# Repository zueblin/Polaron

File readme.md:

# Polaron

Polaron is a DIY digital drum machine based on the [Teensy 3.6](https://www.pjrc.com/teensy/) USB Microcontroller plattform.

Main features:

- 16 step sequencer
- 6 instrument tracks
- 16 patterns per track
- load/save projects to SD card
- 2 pots for parameter control
- parameter locks: all instrument parameters can be recorded for each step
- different pattern length for each instrument track
- sync to midi-clock (usb-midi) or trigger input
- crunchy 12bit stereo outputs
- open source hardware/software: if you miss a feature or are annoyed by a bug... change it!

Disclaimer: This is a DIY project, features may change or not work for you. Use at your own risk.

here's some short videos:

https://www.youtube.com/watch?v=JC_pZTxMb0c

https://vimeo.com/302283771

https://vimeo.com/305113707

Follow the project on Instagram: https://www.instagram.com/polaron.me/

And don't forget to check the [Project WIKI](https://github.com/zueblin/Polaron/wiki) for more info.

## Software

To build the software, the following tools are required:

- [Arduino IDE](https://www.arduino.cc/en/Main/Software) (tested with 1.8.6)
- [Teensyduino Add-On](https://www.pjrc.com/teensy/teensyduino.html) (tested with 1.43)

## Hardware

PCB is designed using KICAD 5.1.2

Parts needed (Rev 1.4):

- Teensy 3.6 32bit Microcontroller (with Headers)
- 30 x WS2812b RGB LEDs (or SK6812)
- 30 x 6x6mm Pushbuttons (ideally 4.3mm height, 100gf) (Mouser: 688-SKHHAJ)
- 16 x 270 ohm throughhole Resistors (Mouser: 603-MF0207FTE52-270R)
- 14 x 270 ohm SMD Resistors (1206 housing)
- 2 x 10k SMD Resistors (1206 housing)
- 1 x 1N4148 diode
- 1 x 2N3904BU transistor
- 4 x SN74HC165N Shiftregister (Mouser: 595-SN74HC165N)
- 2 x ALPS Potentiometer (RK09K1130A8G)
- 2 x 2.2 uF SMD Capacitor (1206 housing, Mouser: 963-TMK316BJ225KL-T)
- 2 x Audio Jack (SJ-352X-SMT)
- 1 x 48 Position / 2 Row IC DIP Socket (Mouser: 517-4848-6004-CP)
- 2 x 20mm PCB Standoff with 3mm thread (Mouser: 534-24437)

Check the Wiki for [Build Instructions](https://github.com/zueblin/Polaron/wiki/Building-the-Polaron)

## Known Issues:
PCB Rev 1.4

- In some situations, when connecting the polaron to a computer via usb and connecting the polaron audio output to an audio interface that is connected to the computer (e.g via thunderbolt), a ground loop is created. This results in a very noticable noise/whine in the audio channel (which is caused by the LED PWM). Tested solution: [Audio Ground Loop Noise Isolator](https://www.pjrc.com/store/audio_ground_isolator.html)

## FAQ

- Q: Is this an easy build? A: This is an intermediate project to build. Its not very complicated, but there are some SMD parts which are not easy to get right (the LEDs). You'll need a decent soldering iron, with a rather fine tip.
- Q: Is this a pro audio project? A: No, not exactly. The Polaron is more about a fun workflow than super hifi sound.
- Q: Does it work with a Teensy 3.5? A: PJRC forum member drjohn reports successfully running the Polaron with a Teensy 3.5.
- Q: Does it work with a Teensy 4.0 / 4.1? A: No, the Polaron relies on the internal DAC of the Teensy 3.6 and is not compatible with Teensy 4.0 / 4.1
- Q: Is there a manual? A: Yes, please check the [Project WIKI](https://github.com/zueblin/Polaron/wiki) for build instructions and operating manual. If you still have questions / suggestions, please send me a mail.
- Q: Does the polaron fit into a euro-rack? A: No, not really (PCB size is 15.7cm x 11.6cm). Polaron builder N.Shaver has experimented with a 3D printable eurorack case for the polaron which he shares on [Thingiverse](https://www.thingiverse.com/thing:3830556)
- Q: Can i buy a PCB? A: Sold out, but let me know if you'd be interested in buying one. ~~Yes, i currently have PCBs at 15 USD (+ shipping from switzerland). Please contact me by email, if interested.~~
- Q: Can i buy a part-kit? A: I don't sell part kits anymore, since it is very easy and efficient to order parts online, eg. from mouser. ~~Yes, i currently have part kits (PCB + all parts, EXCLUDING the teensy itself) at 60 USD incl. untracked international shipping. Add 5 USD for tracked shipping. Please send me a mail, if interested.~~
- Q: Can i buy a fully assembled Polaron? A: Not, not at the moment.
- Q: How can i support this project? A: Spread the word, star the project on github, let your friends know, buy a PCB, build a Polaron and share a video...there are many ways. In general, knowing that this project sparks some interest is what keeps it going!

# License

Code: MIT

Hardware: cc-by-sa-3.0

By: Thomas Zueblin (thomas.zueblin@gmail.com)

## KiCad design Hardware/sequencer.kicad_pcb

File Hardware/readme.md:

# License

Code: MIT

Hardware: cc-by-sa-3.0

By: Thomas Zueblin (thomas.zueblin@gmail.com)

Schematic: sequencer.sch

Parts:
C1, C2: 2.2uF; C_1206_HandSoldering
D1, D2, D3, D4, D5, D6, D7, D8, D9, D10, D11, D12, D13, D14, D15, D16, D17, D18, D19, D20, D21, D22, D23, D24, D25, D26, D27, D28, D29, D30: LED_WS2812B-PLCC4
D31: 1N4148; D_DO-35_SOD27_P2.54mm_Vertical_AnodeUp
IC1, IC2, IC3, IC4: 74HC165N; DIL16
J1, J2: SJ-3523-SMT-TR; CUI_SJ-3523-SMT-TR
Q1: 2N3904; TO-92_Inline_Wide
R1, R2, R3, R4, R5, R6, R7, R8, R9, R10, R11, R12, R13, R14, R15, R16: 270; R_Axial_DIN0411_L9.9mm_D3.6mm_P12.70mm_Horizontal_noSilkscr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
R17, R18, R19, R20, R21, R22, R23, R24, R25, R26, R27, R28, R29, R30: 270; R_1206_HandSoldering
R31, R32: 10k; R_1206_HandSoldering
RV1, RV2: POT; Potentiometer_Alps_RK09K_Horizontal
S1, S2, S3, S4, S5, S6, S7, S8, S9, S10, S11, S12, S13, S14, S15, S16, S17, S18, S19, S20, S21, S22, S23, S24, S25, S26, S27, S28, S29, S30: SWITCH-MOMENTARY-2PTH; TACTILE-PTH
U1: Teensy3.6; Teensy35_36_simple

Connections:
/Audio1: C1.2, J1.3
/Audio2: C2.2, J1.2
/AudioGND: J1.1, U1.52 (AGND)
/JOY_A: RV1.2, U1.50 (23_A9_PWM_Touch)
/JOY_B: RV2.2, U1.49 (22_A8_PWM_Touch)
/LED_IN: D1.4 (DIN), U1.8 (6_PWM)
/LedConn1: D8.2 (DOUT), D9.4 (DIN)
/LedConn2: D16.2 (DOUT), D17.4 (DIN)
/LedConn3: D24.2 (DOUT), D25.4 (DIN)
/SHIFT_CLOCK: IC1.2 (CLK), IC2.2 (CLK), IC3.2 (CLK), IC4.2 (CLK), U1.4 (2_PWM)
/SHIFT_DATA_OUT: IC4.9 (QH), U1.3 (1_TX1_MISO1_Touch)
/SHIFT_PLOAD: IC1.1 (SH/~LD), IC2.1 (SH/~LD), IC3.1 (SH/~LD), IC4.1 (SH/~LD), U1.2 (0_RX1_MOSI1_Touch)
/Trigger-Input: Q1.3, R32.1, U1.30 (33_A14_CAN1TX_scl0)
GND: D1.3 (VSS), D2.3 (VSS), D3.3 (VSS), D4.3 (VSS), D5.3 (VSS), D6.3 (VSS), D7.3 (VSS), D8.3 (VSS), D9.3 (VSS), D10.3 (VSS), D11.3 (VSS), D12.3 (VSS), D13.3 (VSS), D14.3 (VSS), D15.3 (VSS), D16.3 (VSS), D17.3 (VSS), D18.3 (VSS), D19.3 (VSS), D20.3 (VSS), D21.3 (VSS), D22.3 (VSS), D23.3 (VSS), D24.3 (VSS), D25.3 (VSS), D26.3 (VSS), D27.3 (VSS), D28.3 (VSS), D29.3 (VSS), D30.3 (VSS), D31.2, IC1.8 (GND), IC1.15 (INH), IC2.8 (GND), IC2.15 (INH), IC3.8 (GND), IC3.15 (INH), IC4.5 (G), IC4.6 (H), IC4.8 (GND), IC4.15 (INH), J2.1, Q1.1, R1.2, R2.2, R3.2, R4.2, R5.2, R6.2, R7.2, R8.2, R9.2, R10.2, R11.2, R12.2, R13.2, R14.2, R15.2, R16.2, R17.1, R18.1, R19.1, R20.1, R21.1, R22.1, R23.1, R24.1, R25.1, R26.1, R27.1, R28.1, R29.1, R30.1, RV1.3, RV2.3, U1.1 (GND)
unnamed: C1.1, U1.37 (A21_DAC0)
unnamed: C2.1, U1.38 (A22_DAC1)
unnamed: D1.2 (DOUT), D2.4 (DIN)
unnamed: D2.2 (DOUT), D3.4 (DIN)
unnamed: D3.2 (DOUT), D4.4 (DIN)
unnamed: D4.2 (DOUT), D5.4 (DIN)
unnamed: D5.2 (DOUT), D6.4 (DIN)
unnamed: D6.2 (DOUT), D7.4 (DIN)
unnamed: D7.2 (DOUT), D8.4 (DIN)
unnamed: D10.2 (DOUT), D11.4 (DIN)
unnamed: D9.2 (DOUT), D10.4 (DIN)
unnamed: D11.2 (DOUT), D12.4 (DIN)
unnamed: D12.2 (DOUT), D13.4 (DIN)
unnamed: D13.2 (DOUT), D14.4 (DIN)
unnamed: D14.2 (DOUT), D15.4 (DIN)
unnamed: D15.2 (DOUT), D16.4 (DIN)
unnamed: D17.2 (DOUT), D18.4 (DIN)
unnamed: D18.2 (DOUT), D19.4 (DIN)
unnamed: D19.2 (DOUT), D20.4 (DIN)
unnamed: D20.2 (DOUT), D21.4 (DIN)
unnamed: D21.2 (DOUT), D22.4 (DIN)
unnamed: D22.2 (DOUT), D23.4 (DIN)
unnamed: D23.2 (DOUT), D24.4 (DIN)
unnamed: D25.2 (DOUT), D26.4 (DIN)
unnamed: D26.2 (DOUT), D27.4 (DIN)
unnamed: D27.2 (DOUT), D28.4 (DIN)
unnamed: D28.2 (DOUT), D29.4 (DIN)
unnamed: D29.2 (DOUT), D30.4 (DIN)
unnamed: D31.1, Q1.2, R31.2
unnamed: IC1.3 (E), R21.2, S21.3 (2)
unnamed: IC1.4 (F), R22.2, S22.3 (2)
unnamed: IC1.5 (G), R23.2, S23.3 (2)
unnamed: IC1.6 (H), R24.2, S24.3 (2)
unnamed: IC1.9 (QH), IC2.10 (SER)
unnamed: IC1.11 (A), R17.2, S17.3 (2)
unnamed: IC1.12 (B), R18.2, S18.3 (2)
unnamed: IC1.13 (C), R19.2, S19.3 (2)
unnamed: IC1.14 (D), R20.2, S20.3 (2)
unnamed: IC2.3 (E), R13.1, S13.3 (2)
unnamed: IC2.4 (F), R14.1, S14.3 (2)
unnamed: IC2.5 (G), R15.1, S15.3 (2)
unnamed: IC2.6 (H), R16.1, S16.3 (2)
unnamed: IC2.9 (QH), IC3.10 (SER)
unnamed: IC2.11 (A), R9.1, S9.3 (2)
unnamed: IC2.12 (B), R10.1, S10.3 (2)
unnamed: IC2.13 (C), R11.1, S11.3 (2)
unnamed: IC2.14 (D), R12.1, S12.3 (2)
unnamed: IC3.3 (E), R5.1, S5.3 (2)
unnamed: IC3.4 (F), R6.1, S6.3 (2)
unnamed: IC3.5 (G), R7.1, S7.3 (2)
unnamed: IC3.6 (H), R8.1, S8.3 (2)
unnamed: IC3.9 (QH), IC4.10 (SER)
unnamed: IC3.11 (A), R1.1, S1.3 (2)
unnamed: IC3.12 (B), R2.1, S2.3 (2)
unnamed: IC3.13 (C), R3.1, S3.3 (2)
unnamed: IC3.14 (D), R4.1, S4.3 (2)
unnamed: IC4.3 (E), R29.2, S29.3 (2)
unnamed: IC4.4 (F), R30.2, S30.3 (2)
unnamed: IC4.11 (A), R25.2, S25.3 (2)
unnamed: IC4.12 (B), R26.2, S26.3 (2)
unnamed: IC4.13 (C), R27.2, S27.3 (2)
unnamed: IC4.14 (D), R28.2, S28.3 (2)
unnamed: J2.2, R31.1
VCC: D1.1 (VDD), D2.1 (VDD), D3.1 (VDD), D4.1 (VDD), D5.1 (VDD), D6.1 (VDD), D7.1 (VDD), D8.1 (VDD), D9.1 (VDD), D10.1 (VDD), D11.1 (VDD), D12.1 (VDD), D13.1 (VDD), D14.1 (VDD), D15.1 (VDD), D16.1 (VDD), D17.1 (VDD), D18.1 (VDD), D19.1 (VDD), D20.1 (VDD), D21.1 (VDD), D22.1 (VDD), D23.1 (VDD), D24.1 (VDD), D25.1 (VDD), D26.1 (VDD), D27.1 (VDD), D28.1 (VDD), D29.1 (VDD), D30.1 (VDD), IC1.16 (VCC), IC2.16 (VCC), IC3.16 (VCC), IC4.16 (VCC), R32.2, RV1.1, RV2.1, S1.1, S2.1, S3.1, S4.1, S5.1, S6.1, S7.1, S8.1, S9.1, S10.1, S11.1, S12.1, S13.1, S14.1, S15.1, S16.1, S17.1, S18.1, S19.1, S20.1, S21.1, S22.1, S23.1, S24.1, S25.1, S26.1, S27.1, S28.1, S29.1, S30.1, U1.15 (3.3V)

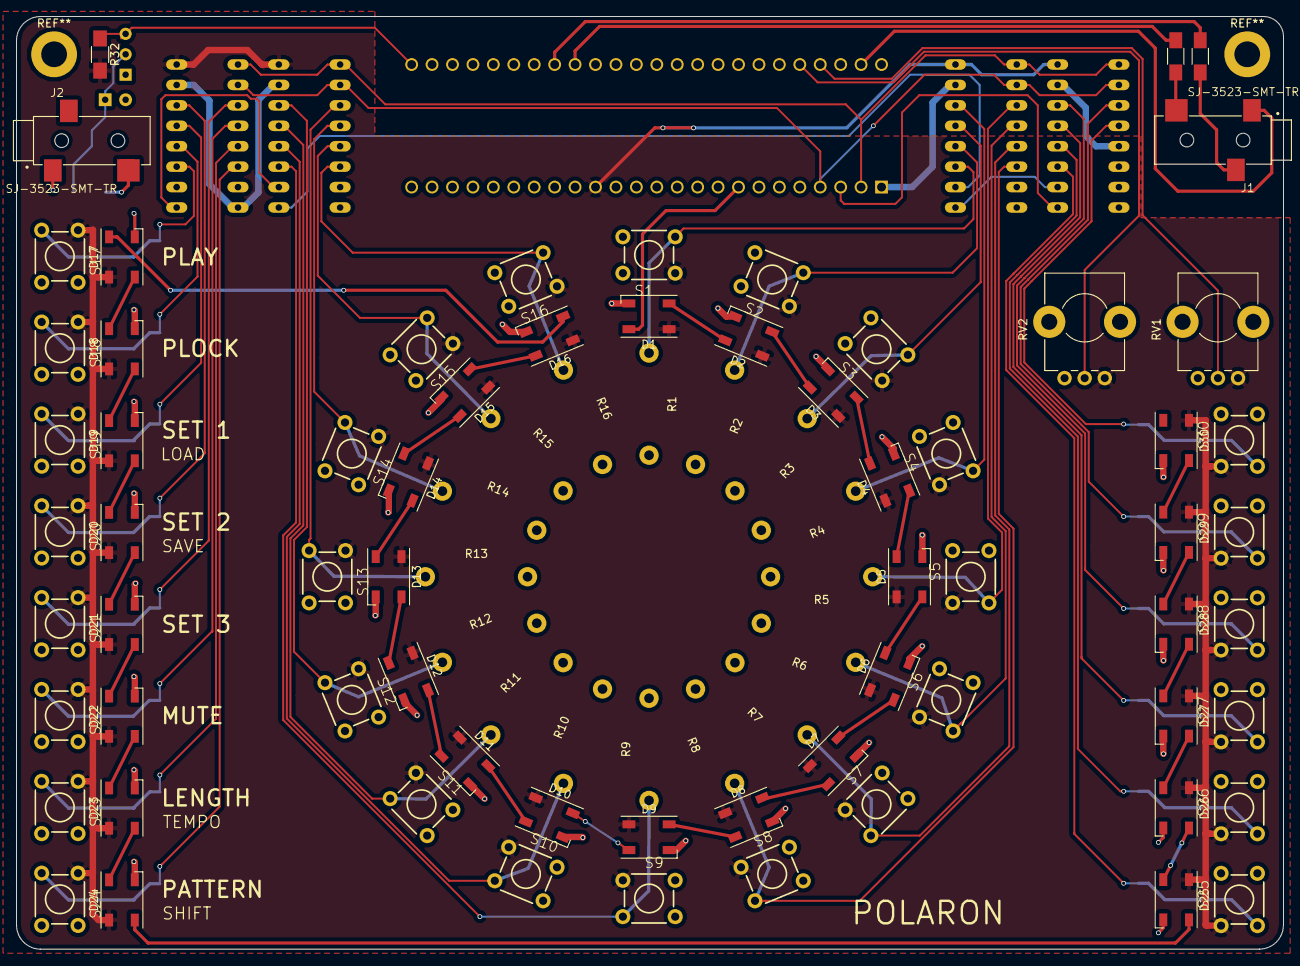
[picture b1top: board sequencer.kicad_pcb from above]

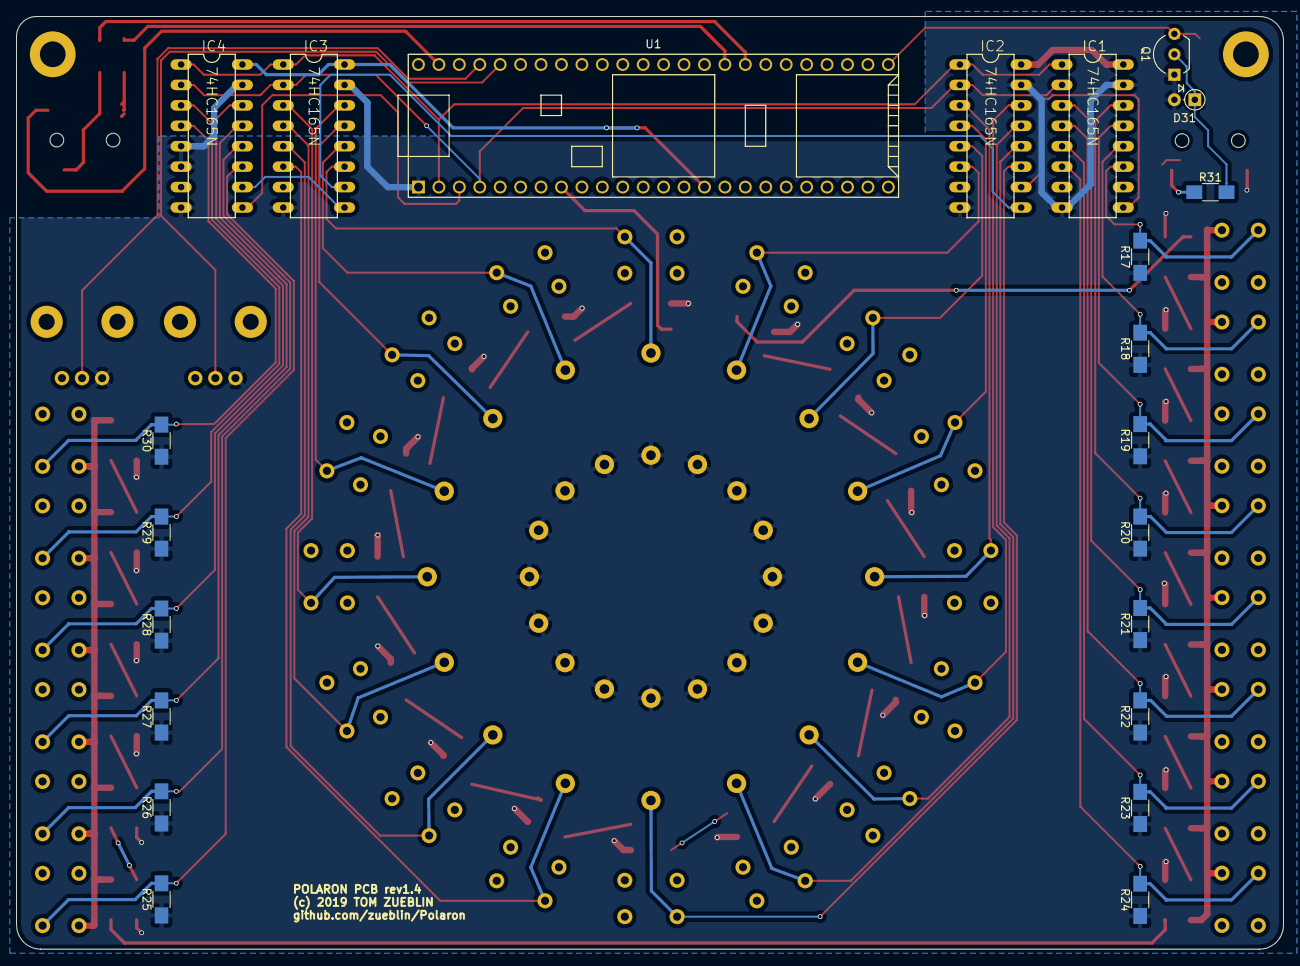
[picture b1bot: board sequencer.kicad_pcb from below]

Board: 2 copper layers, 157.5 x 116.0 mm, 105 parts (22 on the bottom side), 78 nets.

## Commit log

2018-09-16 initial version
2018-09-28 updated codebase to last prototype version
2018-09-28 removed currently unused files
2018-09-29 added AudioChannel class in order to abstract different instrument implementations into a single base class.
2018-10-02 MIT Header added
2018-10-04 added possibility to switch between 3 different parameter sets
2018-10-05 added two new instrument types
2018-10-19 work in progress
2018-10-21 added a variable shape envelope (work in progress)
2018-10-21 cleaned up the variable shape envelope
2018-10-25 added retrigger feature to the variable shape envelope
2018-10-26 license correction
2018-11-01 removed notes file
2018-11-01 combined software and hardware into one polaron repo.
2018-11-01 Added some images and readme
2018-11-01 consistent formatting/tab/space usage across all files
2018-11-01 added a way to configure default settings for each instrument track
2018-11-08 added a Sensor class that wraps the potentiometer input an adds some logic
2018-11-08 moved code out of the main sketch into the sequencer class. added a primitive way to set the tempo while the sequencer is not running.
2018-11-09 - changed default formatter used in vs-code and reformatted all files - tempo control is now handled inside the sequencer class
2018-11-10 - added possibility to switch (and copy-paste) all track patterns at once or each track individually - added a new audiochannel exploring two ringmodulated sinus oscilators
2018-11-11 - changed handling of timing to clock the sequencer - added more audio options to dual-sine channel -
2018-11-15 - changed env to an analog style env that will start the attack at the current env value and not necessarily at zero - fixed some behaviour regarding the timing/clock changes - added a proper kickdru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
2018-11-15 - deactivate inputs when leaving modes - minor adjustments to audio channels
2018-11-22 - added a way to rotate the pattern - unmute all tracks when changing the 'global' pattern - updated readme
2018-11-22 added demo video
2018-11-24 PCB rev 1.2
2018-12-13 added assembly images
2018-12-13 readme adapted
2019-01-17 feature added to control panorama / volume of each instrument channel by pressing down the track select button and turing pot1 for volume / pot2 for channel panning
2019-01-17 added links to wiki and a note about the ground loop problem
2019-01-17 change in readme
2019-02-17 cheatsheet added
2019-02-28 Added pattern model svg
2019-03-03 rev 1.2 pcb images
2019-03-05 added a delay to simpleDrumChannel
2019-03-07 changed simple-delay to accept number of samples as input instead of milliseconds.
2019-03-07 changed the mixer gain settings, so that channels can overdrive when increasing the channel volume
2019-03-07 param_set change buttons are now always slightly illuminated in order for better visibility for this group of buttons
2019-03-14 added firmware compilation documentation
2019-03-14 using a short click sample to fatten up the kick. Adding an example on how one might use pitchable in-memory samples in audio-channels
2019-03-28 - fixed some issues with sequencer stepping / triggering sounds - major cleanup / some refactorings - minor changes in the sound engine
2019-03-28 fixed a problem with midi-sync (polaron would run 1 clock cycle ahead)
2019-03-28 rotated pot 1 / 2 footprint by 180 degrees
2019-03-30 rev 1.3 pcb - Pots rotated by 180 degrees - Added circuit for trigger input
2019-03-31 rearranged some of the audio objects to refect the signal flow, as this apparently has an effect on the latency of the instrument
2019-04-04 trying to add interactive svg to the manual
2019-04-04 added LED ordering image
2019-04-04 added led-order svg
2019-04-04 - Start/Stop LED now blinks in tempo, when the sequencer is stopped - Slightly tuned the activate/deactivate behaviour of the Potentiometers, as they would sometimes activate themselves (noise in the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
2019-04-04 avoid triggerless plocked steps: when toggling plock mode for individual steps: if plock is turned on for a step that doesnt have a trigger set, set a trigger
2019-04-06 changed ordering of parameters in boomchannel to better group according to functions fixed a problem where the volume could change unintended on channels that have parameter lock recording on
2019-04-07 simplified and cleaned up handling of the possibilities to clocking the sequencer. added possibility to react to trigger inputs (needs new hardware)
2019-04-07 when input1 or 2 is active, this is now indicated by a red parameter lock LED instead of blinking / non-blinkin
2019-04-08 adjusted parameter setting in the boom channel
2019-04-11 Boom channel now allows negative frequency modulation. Also adjusted default values
2019-04-11 removed obsolete comment
2019-04-19 step state / plock state is stored as part of the pattern, in order to quickly calculate if any steps are triggers / or algorithmically change the whole pattern (e.g bitshift the pattern)
2019-04-19 feat: added dignostic mode that allows to check if a build is correctly working (LEDs, buttons, pots, audio output). dignostic mode can be entered by pressing and holding track button 5 (button close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
2019-04-25 feat: tempo is now changed by pressing and holding SET_PATTERN_LENGTH and SWITCH_PATTERN buttons at the same time. When in this mode, the track buttons allow to change the tempo in small increments (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
2019-04-25 minor change
2019-04-26 changed cheatsheet to reflect latest features
2019-05-09 Bugfix: Fixed a problem where after rotating a pattern, the sequencer would not play the correct triggers anymore
2019-05-12 refactored clock handling / ticking the sequencer into a separate class
2019-06-13 Moved most timing logic into a new clock class. Swing now also supported when clocking the polaron to midi-clock. Trigger input now uses an interrupt to detect pulses, so that none of them should be 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
2019-06-13 added swing function to cheatsheet
2019-06-13 added changelog
2019-06-13 Polaron appears now as 'Polaron' when using usbMidi
2019-06-15 implemented a first draft for loading / storing the sequencer state to SD card as json object
2019-06-15 load / store data in chunks as to not exceed available memory
2019-06-16 [FIX] fixed a problem where copy pasting a pattern did not copy the full state of the source pattern onto the destination pattern
2019-06-16 [FIX] fixed a problem where copy pasting a pattern did not copy the full state of the source pattern onto the destination pattern [INTERNAL] stopped using a static int for state handling in tracks
2019-06-20 [INTERNAL] wip load/and save
2019-06-20 Hardware Rev 1.4: Function buttons and track buttons now use SMD Resistors, so that there is space on the PCB for text labels for each function button
2019-06-27 WIP pattern load / save
2019-06-27 cheatsheet updated
2019-07-03 added a5 refcard
2019-07-06 added a way to end plock mode by going back to the pattern as it was before entering the mode (undo)
2019-07-25 changed the way the shift button presses work: its now enough to press shift when entering a mode, after that the shift button can be released and the mode is still in shift mode
2019-07-25 documentation (build images) adapted for revision 1.4
2019-07-25 main page images adapted for rev 1.4
2019-07-25 added changes for rev 1.3 and 1.4 PCB
2019-07-25 readme adapted for new revision
2019-07-28 - store channel gain / pan with project save - turn on / off midi out via define
2019-08-15 cheatsheet updated to rev1.4
2019-09-05 - tempo and swing is now also stored when a project is saved - reverted the p-lock undo pattern function, as it doesnt belong in this branch (might pick it up again later)
2019-09-05 readme / changelog adapted
2020-04-09 add usb host and names
2020-04-11 merged changes from okyeron-usbhost
2020-04-11 allow usbhost feature to be switched on/off during compilation
2020-04-13 allow a step to be triggered only every n'th time when a pattern loops
2020-04-13 implemented setting the trigger conditions as a fourth parameter set
2020-05-15 BroadBandNoiseChannel replaced with BapChannel
2020-05-15 Each Channel now stores its own default values, which makes it easier to use different channels by commenting them in/out in Polaron.ino
2020-05-15 changed project naming for SD card, since the SD lib cannot handle long filenames.

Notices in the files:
Hardware/sequencer.kicad_pcb:
(c) 2019 TOM ZUEBLIN
